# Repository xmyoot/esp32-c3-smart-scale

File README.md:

# ESP32-C3 Smart Scale

A low-power Wi-Fi/BLE smart-scale main board, designed natively in **KiCad 10**. It has a 24-bit load-cell front end, USB-C Li-ion charging, an external antenna and a ~35 µA standby budget.

| | |
|---|---|
| MCU | ESP32-C3-MINI-1U-H4 (Wi-Fi + BLE 5, U.FL external antenna, native USB) |
| Load-cell ADC | HX711, 10 SPS. Excitation is regulated by an external PNP and switched off in power-down |
| Power | USB-C → MCP73831 1S Li-ion charger (455 mA) → TLV75530 3.0 V low-Iq LDO |
| Battery gauge | 1 MΩ / 330 kΩ divider into the ESP32 ADC |
| Protection | USBLC6-2SC6 on USB D± / VBUS, 5.1 kΩ CC pull-downs |
| Programming | USB Serial/JTAG over USB-C, plus 7 underside pogo pads for a factory fixture |
| PCB | 52 × 38 mm, 2 layers, JLCPCB standard rules, 4 × M2 holes, single-sided SMT |
| Status | **Rev A, fab-ready**: ERC 0, DRC 0, schematic↔PCB parity 0, 100 % routed |

## Repository layout

```text
kicad/                       KiCad 10 project (open esp32-c3-smart-scale.kicad_pro)
  lib/smart_scale.*          project symbols, footprints, 3D models (ESP32-C3-MINI-1U, HX711, pogo pads)
fab/
  esp32-c3-smart-scale-gerbers.zip   Gerbers + Excellon drill (upload to JLCPCB)
  assembly/bom_jlcpcb.csv            BOM with LCSC part numbers
  assembly/cpl_jlcpcb.csv            pick-and-place (board origin = bottom-left)
  schematic.pdf, esp32-c3-smart-scale.step
docs/
  architecture.md            system architecture, design decisions, power budget
  design_review.md           ERC/DRC/parity + kicad-happy review results and hand calcs
  bring_up_notes.md          first-power, charging, flashing, load-cell and sleep-current procedure
  client_request.md, design_brief.html
  images/                    schematic and PCB renders
  legacy_tscircuit/          notes from the earlier tscircuit prototype
```

The original tscircuit prototype (`index.circuit.tsx`, `imports/`, `src/`, `dist/`) is kept for reference only. The KiCad project is the source of truth.

## Schematic

The schematic is a single A3 sheet, wired by signal flow: USB-C → ESD/charger → battery/LDO → MCU → load-cell ADC.

## PCB

| Top copper | Bottom copper |
|---|---|
|  |  |

The layout has three zones:

- **RF:** the module sits top-right with its U.FL at the edge.
- **Power:** USB-C, charger and battery sit bottom-right and centre.
- **Analog:** the HX711 and load-cell connector sit on the left, away from the radio.

Both layers carry solid GND pours, stitched with about 110 vias.

## Ordering (JLCPCB)

1. Upload `fab/esp32-c3-smart-scale-gerbers.zip`: 2 layers, 1.6 mm, HASL or ENIG.
2. PCBA, top side: upload `fab/assembly/bom_jlcpcb.csv` and `fab/assembly/cpl_jlcpcb.csv`. Check part rotations in JLC's preview, especially the SOT-23 parts and the USB-C.
3. Hand-fit or order the harnesses: 1S Li-ion with a JST PH 2-pin plug (pin 1 = BAT+), a 4-wire load cell on JST PH 4-pin, and a 2.4 GHz U.FL antenna.

## Toolchain

- KiCad 10.0.7: schematic capture, layout, DRC/ERC, fab outputs.
- [KiCadRoutingTools](https://github.com/drandyhaas/KiCadRoutingTools): completed the local nets after the power/USB/bus trunks were hand-placed.
- [kicad-happy](https://github.com/aklofas/kicad-happy): schematic, PCB and Gerber design-review analyzers, plus LCSC part verification.

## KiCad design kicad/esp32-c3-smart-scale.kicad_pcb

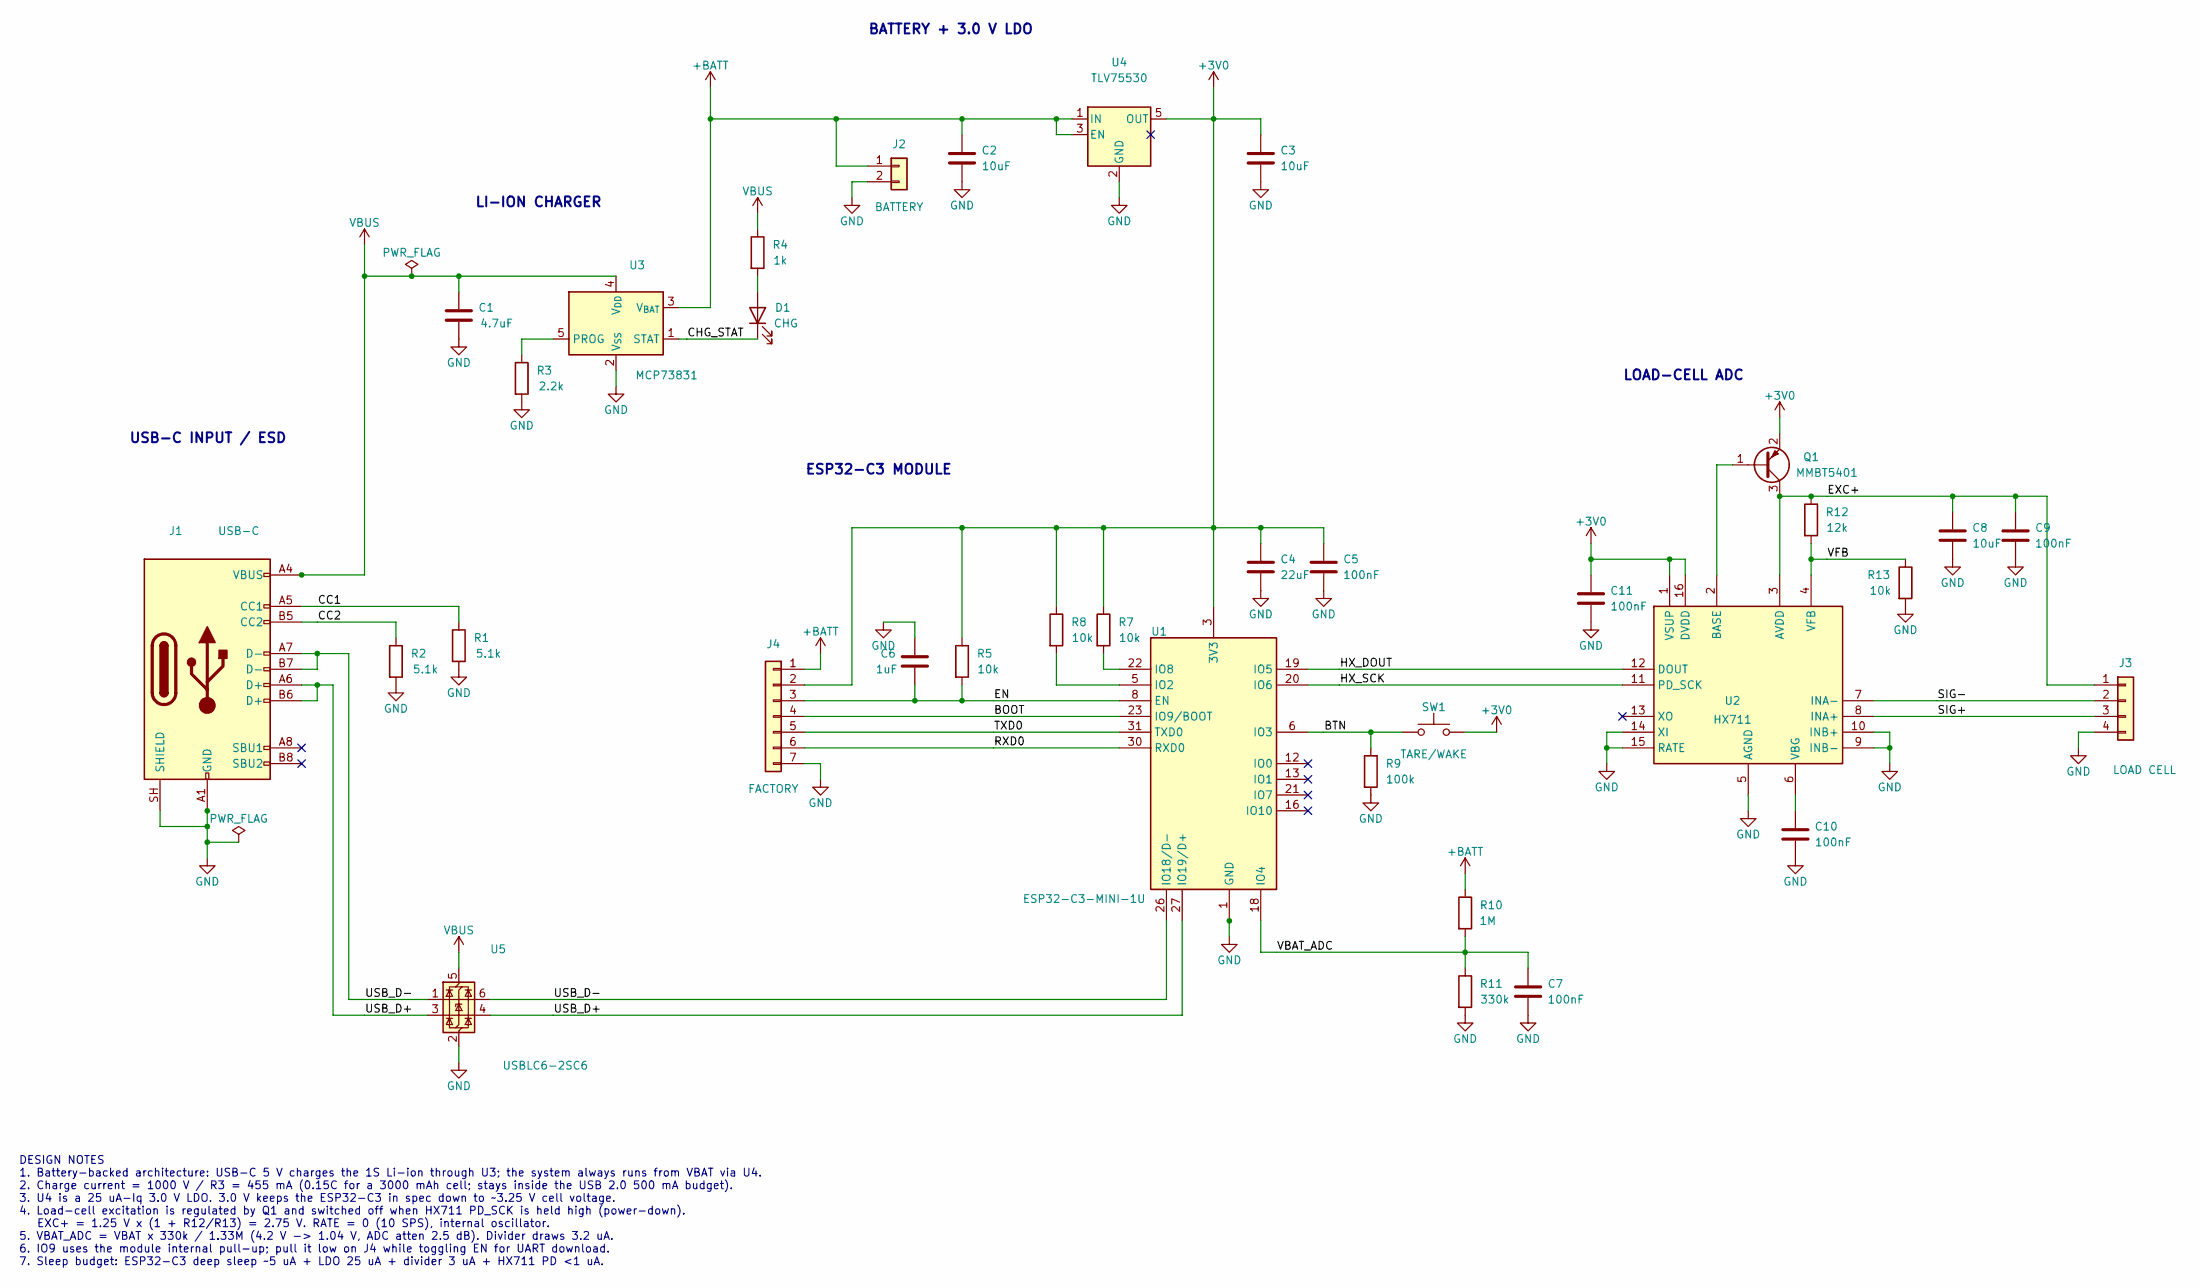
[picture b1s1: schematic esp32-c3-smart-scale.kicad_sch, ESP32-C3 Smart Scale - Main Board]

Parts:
C1: 4.7uF; C_0603_1608Metric; MPN CL10A475KO8NNNC; LCSC C19666
C2, C3, C8: 10uF; C_0603_1608Metric; MPN CL10A106KP8NNNC; LCSC C19702
C4: 22uF; C_0805_2012Metric; MPN CL21A226MAQNNNE; LCSC C45783
C5, C7, C9, C10, C11: 100nF; C_0402_1005Metric; MPN CL05B104KO5NNNC; LCSC C1525
C6: 1uF; C_0402_1005Metric; MPN CL05A105KA5NQNC; LCSC C52923
D1: CHG; LED_0603_1608Metric; MPN KT-0603R; LCSC C2286
J1: USB-C; USB_C_Receptacle_HRO_TYPE-C-31-M-12; MPN TYPE-C-31-M-12; LCSC C165948
J2: BATTERY; JST_PH_S2B-PH-SM4-TB_1x02-1MP_P2.00mm_Horizontal; MPN S2B-PH-SM4-TB(LF)(SN); LCSC C295747
J3: LOAD CELL; JST_PH_S4B-PH-SM4-TB_1x04-1MP_P2.00mm_Horizontal; MPN S4B-PH-SM4-TB(LF)(SN); LCSC C265102
J4: FACTORY; FactoryPads_1x07_P2.54mm; MPN Bare pogo pads (no part)
Q1: MMBT5401; SOT-23; MPN MMBT5401; LCSC C8326
R1, R2: 5.1k; R_0402_1005Metric; MPN 0402WGF5101TCE; LCSC C25905
R3: 2.2k; R_0402_1005Metric; MPN 0402WGF2201TCE; LCSC C25879
R4: 1k; R_0402_1005Metric; MPN 0402WGF1001TCE; LCSC C11702
R5, R7, R8, R13: 10k; R_0402_1005Metric; MPN 0402WGF1002TCE; LCSC C25744
R9: 100k; R_0402_1005Metric; MPN 0402WGF1003TCE; LCSC C25741
R10: 1M; R_0402_1005Metric; MPN 0402WGF1004TCE; LCSC C26083
R11: 330k; R_0402_1005Metric; MPN 0402WGF3303TCE; LCSC C25778
R12: 12k; R_0402_1005Metric; MPN 0402WGF1202TCE; LCSC C25752
SW1: TARE/WAKE; SW_Push_1P1T_XKB_TS-1187A; MPN TS-1187A-B-A-B; LCSC C318884
U1: ESP32-C3-MINI-1U; MPN ESP32-C3-MINI-1U-H4; LCSC C3013922
U2: HX711; SOIC-16_3.9x9.9mm_P1.27mm; MPN HX711; LCSC C43656
U3: MCP73831; SOT-23-5; MPN MCP73831T-2ACI/OT; LCSC C424093
U4: TLV75530; SOT-23-5; MPN TLV75530PDBVR; LCSC C507268
U5: USBLC6-2SC6; SOT-23-6; MPN USBLC6-2SC6; LCSC C7519

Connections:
+3V0: C3.1, C4.1, C5.1, C11.1, J4.2, Q1.2 (E), R5.1, R7.1, R8.1, SW1.2, U1.3 (3V3), U2.1 (VSUP), U2.16 (DVDD), U4.5 (OUT)
+BATT: C2.1, J2.1, J4.1, R10.1, U3.3 (V_{BAT}), U4.1 (IN), U4.3 (EN)
/BOOT: J4.4, U1.23 (IO9/BOOT)
/BTN: R9.1, SW1.1, U1.6 (IO3)
/CC1: J1.A5 (CC1), R1.1
/CC2: J1.B5 (CC2), R2.1
/CHG_STAT: D1.1 (K), U3.1 (STAT)
/EN: C6.2, J4.3, R5.2, U1.8 (EN)
/EXC+: C8.1, C9.1, J3.1, Q1.3 (C), R12.1, U2.3 (AVDD)
/HX_DOUT: U1.19 (IO5), U2.12 (DOUT)
/HX_SCK: U1.20 (IO6), U2.11 (PD_SCK)
/RXD0: J4.6, U1.30 (RXD0)
/SIG+: J3.3, U2.8 (INA+)
/SIG-: J3.2, U2.7 (INA-)
/TXD0: J4.5, U1.31 (TXD0)
/USB_D+: J1.A6 (D+), J1.B6 (D+), U1.27 (IO19/D+), U5.3 (I/O2), U5.4 (I/O2)
/USB_D-: J1.A7 (D-), J1.B7 (D-), U1.26 (IO18/D-), U5.1 (I/O1), U5.6 (I/O1)
/VBAT_ADC: C7.1, R10.2, R11.1, U1.18 (IO4)
/VFB: R12.2, R13.1, U2.4 (VFB)
GND: C1.2, C2.2, C3.2, C4.2, C5.2, C6.1, C7.2, C8.2, C9.2, C10.2, C11.2, J1.A1 (GND), J1.A12 (GND), J1.B1 (GND), J1.B12 (GND), J1.SH (SHIELD), J2.2, J3.4, J4.7, R1.2, R2.2, R3.2, R9.2, R11.2, R13.2, U1.1 (GND), U1.2 (GND), U1.11 (GND), U1.14 (GND), U1.36 (GND), U1.37 (GND), U1.38 (GND), U1.39 (GND), U1.40 (GND), U1.41 (GND), U1.42 (GND), U1.43 (GND), U1.44 (GND), U1.45 (GND), U1.46 (GND), U1.47 (GND), U1.48 (GND), U1.49 (GND), U1.50 (GND), U1.51 (GND), U1.52 (GND), U1.53 (GND), U1.54 (GND), U1.55 (GND), U1.56 (GND), U1.57 (GND), U1.58 (GND), U1.59 (GND), U1.60 (GND), U1.61 (GND), U2.5 (AGND), U2.9 (INB-), U2.10 (INB+), U2.14 (XI), U2.15 (RATE), U3.2 (V_{SS}), U4.2 (GND), U5.2 (GND)
unnamed: D1.2 (A), R4.2
unnamed: Q1.1 (B), U2.2 (BASE)
unnamed: R8.2, U1.5 (IO2)
unnamed: R7.2, U1.22 (IO8)
unnamed: C10.1, U2.6 (VBG)
unnamed: R3.1, U3.5 (PROG)
VBUS: C1.1, J1.A4 (VBUS), J1.A9 (VBUS), J1.B4 (VBUS), J1.B9 (VBUS), R4.1, U3.4 (V_{DD}), U5.5 (VBUS)

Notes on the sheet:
DESIGN NOTES 1. Battery-backed architecture: USB-C 5 V charges the 1S Li-ion through U3; the system always runs from VBAT via U4. 2. Charge current = 1000 V / R3 = 455 mA (0.15C for a 3000 mAh cell; stays inside the USB 2.0 500 mA budget). 3. U4 is a 25 uA-Iq 3.0 V LDO. 3.0 V keeps the ESP32-C3 in 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
USB-C INPUT / ESD
LI-ION CHARGER
BATTERY + 3.0 V LDO
ESP32-C3 MODULE
LOAD-CELL ADC

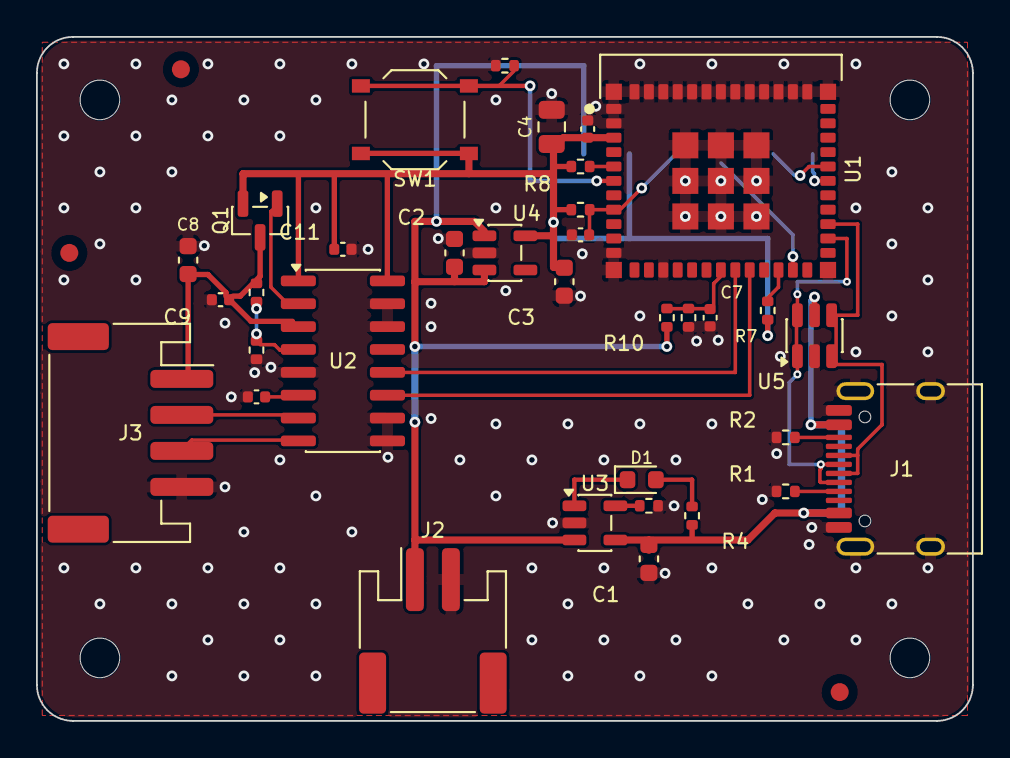
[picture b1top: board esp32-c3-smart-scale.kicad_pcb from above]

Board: 2 copper layers, 52.0 x 38.0 mm, 42 parts (1 on the bottom side), 27 nets.

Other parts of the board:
FID1, FID2, FID3: Fiducial_1mm_Mask2mm
H1, H2, H3, H4: MountingHole_2.2mm_M2

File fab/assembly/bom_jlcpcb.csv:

Comment,Designator,Footprint,LCSC Part #,MPN,Qty
4.7uF,C1,C_0603_1608Metric,C19666,CL10A475KO8NNNC,1
10uF,"C2,C3,C8",C_0603_1608Metric,C19702,CL10A106KP8NNNC,3
22uF,C4,C_0805_2012Metric,C45783,CL21A226MAQNNNE,1
100nF,"C5,C7,C9,C10,C11",C_0402_1005Metric,C1525,CL05B104KO5NNNC,5
1uF,C6,C_0402_1005Metric,C52923,CL05A105KA5NQNC,1
CHG,D1,LED_0603_1608Metric,C2286,KT-0603R,1
USB-C,J1,USB_C_Receptacle_HRO_TYPE-C-31-M-12,C165948,TYPE-C-31-M-12,1
BATTERY,J2,JST_PH_S2B-PH-SM4-TB_1x02-1MP_P2.00mm_Horizontal,C295747,S2B-PH-SM4-TB(LF)(SN),1
LOAD CELL,J3,JST_PH_S4B-PH-SM4-TB_1x04-1MP_P2.00mm_Horizontal,C265102,S4B-PH-SM4-TB(LF)(SN),1
MMBT5401,Q1,SOT-23,C8326,MMBT5401,1
5.1k,"R1,R2",R_0402_1005Metric,C25905,0402WGF5101TCE,2
2.2k,R3,R_0402_1005Metric,C25879,0402WGF2201TCE,1
1k,R4,R_0402_1005Metric,C11702,0402WGF1001TCE,1
10k,"R5,R7,R8,R13",R_0402_1005Metric,C25744,0402WGF1002TCE,4
100k,R9,R_0402_1005Metric,C25741,0402WGF1003TCE,1
1M,R10,R_0402_1005Metric,C26083,0402WGF1004TCE,1
330k,R11,R_0402_1005Metric,C25778,0402WGF3303TCE,1
12k,R12,R_0402_1005Metric,C25752,0402WGF1202TCE,1
TARE/WAKE,SW1,SW_Push_1P1T_XKB_TS-1187A,C318884,TS-1187A-B-A-B,1
ESP32-C3-MINI-1U,U1,ESP32-C3-MINI-1U,C3013922,ESP32-C3-MINI-1U-H4,1
HX711,U2,SOIC-16_3.9x9.9mm_P1.27mm,C43656,HX711,1
MCP73831,U3,SOT-23-5,C424093,MCP73831T-2ACI/OT,1
TLV75530,U4,SOT-23-5,C507268,TLV75530PDBVR,1
USBLC6-2SC6,U5,SOT-23-6,C7519,USBLC6-2SC6,1

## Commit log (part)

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2026-04-02 Scaffold repo and source smart-scale parts
2026-04-02 Implement smart-scale board and validate layout
2026-04-02 Document outputs and current build status
2026-04-02 Reduce autorouter failures and refresh outputs
